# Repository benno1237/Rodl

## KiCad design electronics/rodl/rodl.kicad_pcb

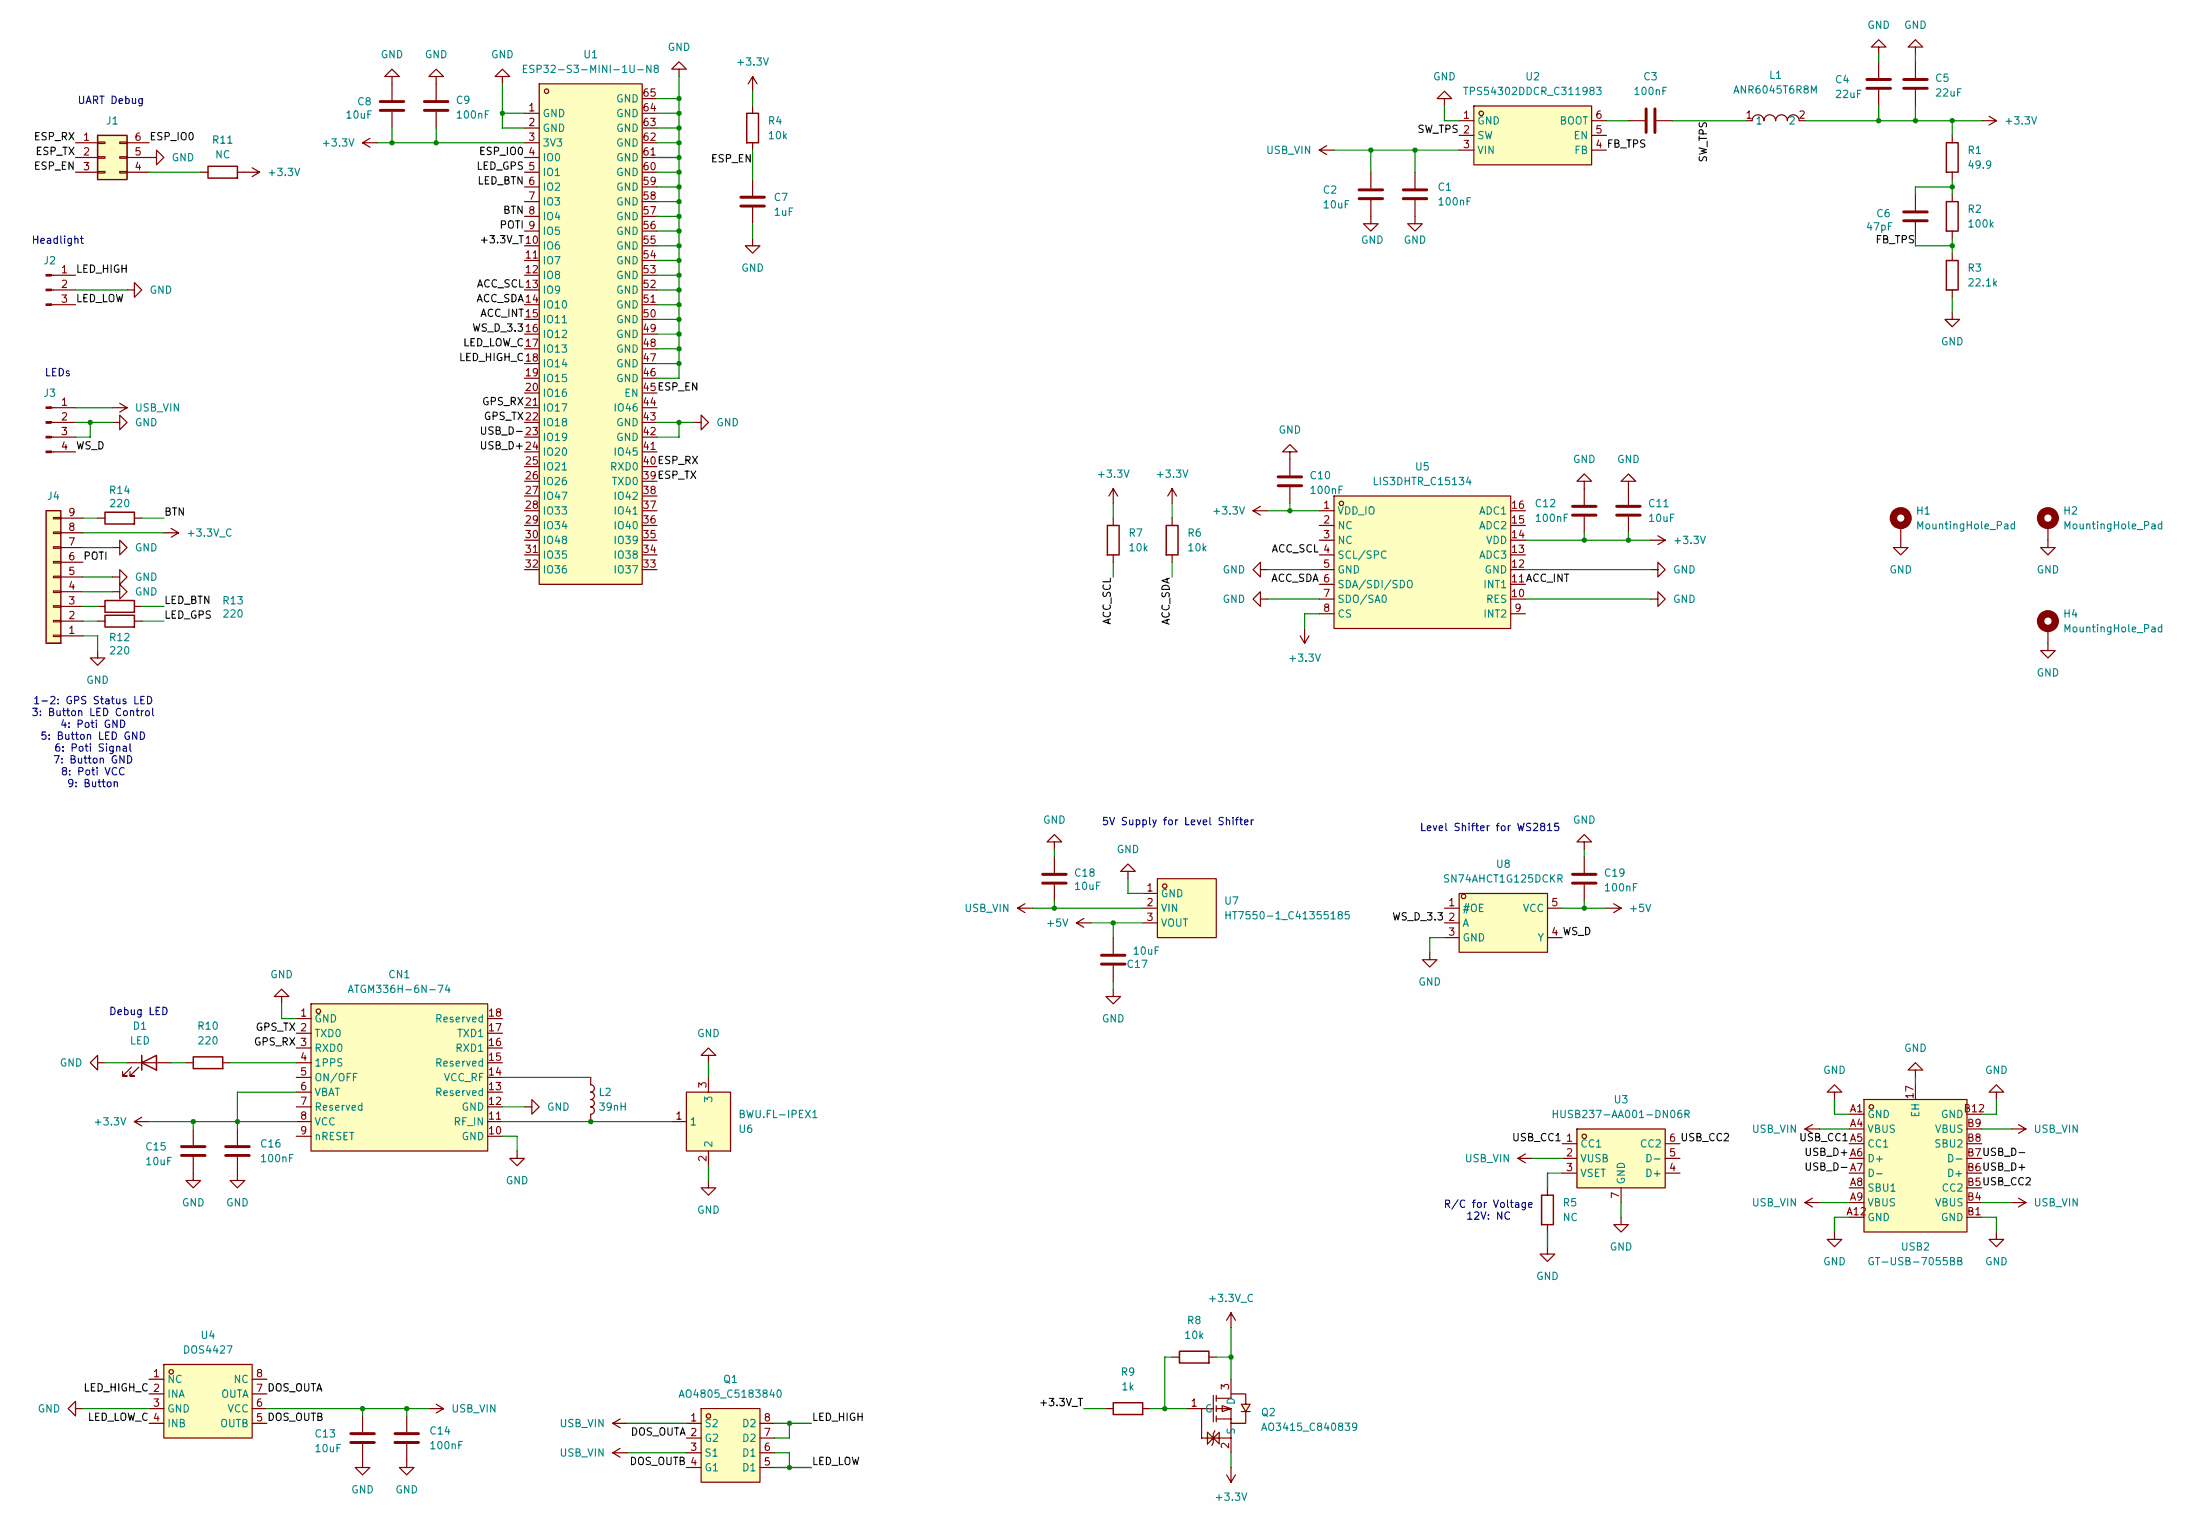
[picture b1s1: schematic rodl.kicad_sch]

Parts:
C1, C3, C9, C10, C12, C14, C16, C19: 100nF; C_0603_1608Metric
C2, C8, C11, C13, C15, C17, C18: 10uF; C_0603_1608Metric
C4, C5: 22uF; C_0805_2012Metric
C6: 47pF; C_0603_1608Metric
C7: 1uF; C_0603_1608Metric
CN1: ATGM336H-6N-74; COMM-SMD_18P-L10.1-W9.7-P1.1-TL_L76-LB; LCSC Part C5804601
D1: LED; LED_0603_1608Metric
H1, H2, H4: MountingHole_Pad; MountingHole_2.5mm_Pad_TopOnly
J1: PinSocket_2x03_P2.54mm_Vertical
J2: Conn_01x03_Pin; PinSocket_1x03_P2.00mm_Vertical
J3: Conn_01x04_Pin; PinSocket_1x04_P2.00mm_Vertical
J4: Conn_01x09; Connector_Rodl
L1: ANR6045T6R8M; IND-SMD_L6.0-W6.0_ANR6045; LCSC Part C6808110
L2: 39nH; L_0603_1608Metric
Q1: AO4805_C5183840; SOP-8_L4.9-W3.9-P1.27-LS6.0-BL; LCSC Part C5183840
Q2: AO3415_C840839; SOT-23-3_L2.9-W1.6-P1.90-LS2.8-BR; LCSC Part C840839
R1: 49.9; R_0603_1608Metric
R2: 100k; R_0603_1608Metric
R3: 22.1k; R_0603_1608Metric
R4, R6, R7, R8: 10k; R_0603_1608Metric
R5, R11: NC; R_0603_1608Metric
R9: 1k; R_0603_1608Metric
R10, R12, R13, R14: 220; R_0603_1608Metric
U1: ESP32-S3-MINI-1U-N8; BULETM-SMD_ESPRESSIF_ESP32-S3-MINI-1U-N8; LCSC Part C2980299
U2: TPS54302DDCR_C311983; SOT-23-6_L2.9-W1.6-P0.95-LS2.8-BL; LCSC Part C311983
U3: HUSB237-AA001-DN06R; TDFN-6_L2.0-W2.0-P0.65-TL-EP; LCSC Part C22373734
U4: DOS4427; SOIC-8_L5.0-W4.0-P1.27-LS6.0-BL; LCSC Part C42395831
U5: LIS3DHTR_C15134; LGA-16_L3.0-W3.0-P0.50-TL; LCSC Part C15134
U6: BWU.FL-IPEX1; IPEX-SMD_BWIPX-1-001E; LCSC Part C5137195
U7: HT7550-1_C41355185; SOT-89-3_L4.5-W2.4-P1.50-LS4.0-BR; LCSC Part C41355185
U8: SN74AHCT1G125DCKR; SC-70-5_L2.0-W1.3-P0.65-LS2.1-BL; LCSC Part C350557
USB2: GT-USB-7055BB; USB-C-TH_GT-USB-7055BB; LCSC Part C7450621

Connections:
+3.3V: C4.2, C5.2, C8.1, C9.1, C10.1, C11.1, C12.1, C15.1, C16.1, CN1.6 (VBAT), CN1.8 (VCC), L1.2, Q2.2 (S), R1.1, R4.1, R6.1, R7.1, R11.2, U1.3 (3V3), U5.1 (VDD_IO), U5.8 (CS), U5.14 (VDD)
+3.3V_C: J4.8, Q2.3 (D), R8.2
+5V: C17.1, C19.1, U7.3 (VOUT), U8.5 (VCC)
/+3.3V_T: R9.1, U1.10 (IO6)
/ACC_INT: U1.15 (IO11), U5.11 (INT1)
/ACC_SCL: R7.2, U1.13 (IO9), U5.4 (SCL/SPC)
/ACC_SDA: R6.2, U1.14 (IO10), U5.6 (SDA/SDI/SDO)
/BTN: R14.2, U1.8 (IO4)
/DOS_OUTA: Q1.2 (G2), U4.7 (OUTA)
/DOS_OUTB: Q1.4 (G1), U4.5 (OUTB)
/ESP_EN: C7.1, J1.3, R4.2, U1.45 (EN)
/ESP_IO0: J1.6, U1.4 (IO0)
/ESP_RX: J1.1, U1.40 (RXD0)
/ESP_TX: J1.2, U1.39 (TXD0)
/FB_TPS: C6.2, R2.2, R3.1, U2.4 (FB)
/GPS_RX: CN1.3 (RXD0), U1.21 (IO17)
/GPS_TX: CN1.2 (TXD0), U1.22 (IO18)
/LED_BTN: R13.2, U1.6 (IO2)
/LED_GPS: R12.2, U1.5 (IO1)
/LED_HIGH: J2.1, Q1.7 (D2), Q1.8 (D2)
/LED_HIGH_C: U1.18 (IO14), U4.2 (INA)
/LED_LOW: J2.3, Q1.5 (D1), Q1.6 (D1)
/LED_LOW_C: U1.17 (IO13), U4.4 (INB)
/POTI: J4.6, U1.9 (IO5)
/SW_TPS: C3.2, L1.1, U2.2 (SW)
/USB_CC1: U3.1 (CC1), USB2.A5 (CC1)
/USB_CC2: U3.6 (CC2), USB2.B5 (CC2)
/USB_D+: U1.24 (IO20), USB2.A6 (D+), USB2.B6 (D+)
/USB_D-: U1.23 (IO19), USB2.A7 (D-), USB2.B7 (D-)
/WS_D: J3.4, U8.4 (Y)
/WS_D_3.3: U1.16 (IO12), U8.2 (A)
GND: C1.2, C2.2, C4.1, C5.1, C7.2, C8.2, C9.2, C10.2, C11.2, C12.2, C13.2, C14.2, C15.2, C16.2, C17.2, C18.1, C19.2, CN1.1 (GND), CN1.10 (GND), CN1.12 (GND), D1.1 (K), H1.1, H2.1, H4.1, J1.5, J2.2, J3.2, J3.3, J4.1, J4.4, J4.5, J4.7, R3.2, R5.2, U1.1 (GND), U1.2 (GND), U1.42 (GND), U1.43 (GND), U1.46 (GND), U1.47 (GND), U1.48 (GND), U1.49 (GND), U1.50 (GND), U1.51 (GND), U1.52 (GND), U1.53 (GND), U1.54 (GND), U1.55 (GND), U1.56 (GND), U1.57 (GND), U1.58 (GND), U1.59 (GND), U1.60 (GND), U1.61 (GND), U1.62 (GND), U1.63 (GND), U1.64 (GND), U1.65 (GND), U2.1 (GND), U3.7 (GND), U4.3 (GND), U5.5 (GND), U5.7 (SDO/SA0), U5.10 (RES), U5.12 (GND), U6.2, U6.3, U7.1 (GND), U8.3 (GND), USB2.17 (EH), USB2.A1 (GND), USB2.A12 (GND), USB2.B1 (GND), USB2.B12 (GND)
unnamed: C6.1, R1.2, R2.1
unnamed: CN1.4 (1PPS), R10.2
unnamed: CN1.11 (RF_IN), L2.2, U6.1
unnamed: CN1.14 (VCC_RF), L2.1
unnamed: D1.2 (A), R10.1
unnamed: J1.4, R11.1
unnamed: J4.2, R12.1
unnamed: J4.3, R13.1
unnamed: J4.9, R14.1
unnamed: Q2.1 (G), R8.1, R9.2
unnamed: C3.1, U2.6 (BOOT)
unnamed: R5.1, U3.3 (VSET)
USB_VIN: C1.1, C2.1, C13.1, C14.1, C18.2, J3.1, Q1.1 (S2), Q1.3 (S1), U2.3 (VIN), U3.2 (VUSB), U4.6 (VCC), U7.2 (VIN), USB2.A4 (VBUS), USB2.A9 (VBUS), USB2.B4 (VBUS), USB2.B9 (VBUS)

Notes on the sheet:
LEDs
R/C for Voltage 12V: NC
Headlight
1-2: GPS Status LED 3: Button LED Control 4: Poti GND 5: Button LED GND 6: Poti Signal 7: Button GND 8: Poti VCC 9: Button
Level Shifter for WS2815
Debug LED
UART Debug
5V Supply for Level Shifter

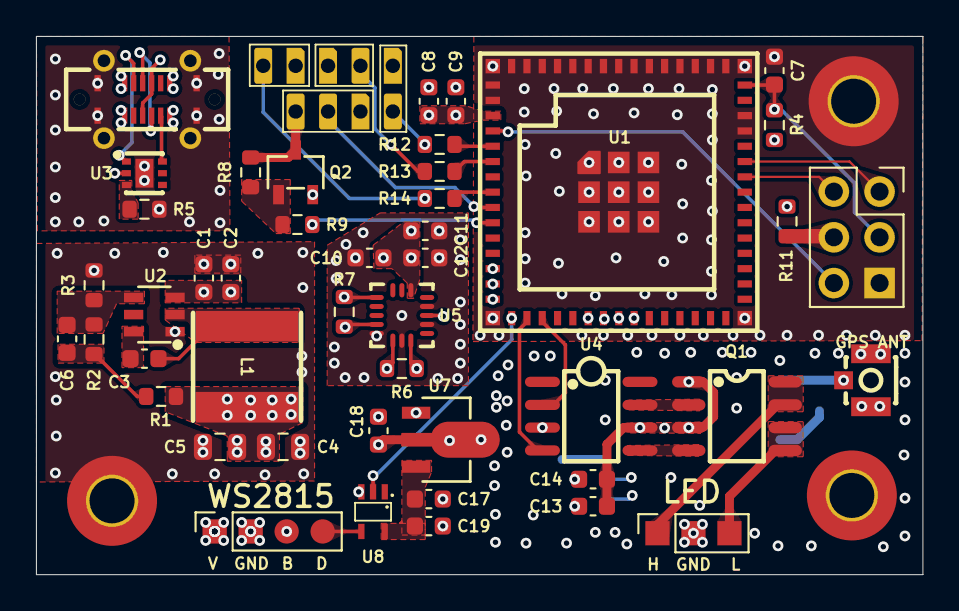
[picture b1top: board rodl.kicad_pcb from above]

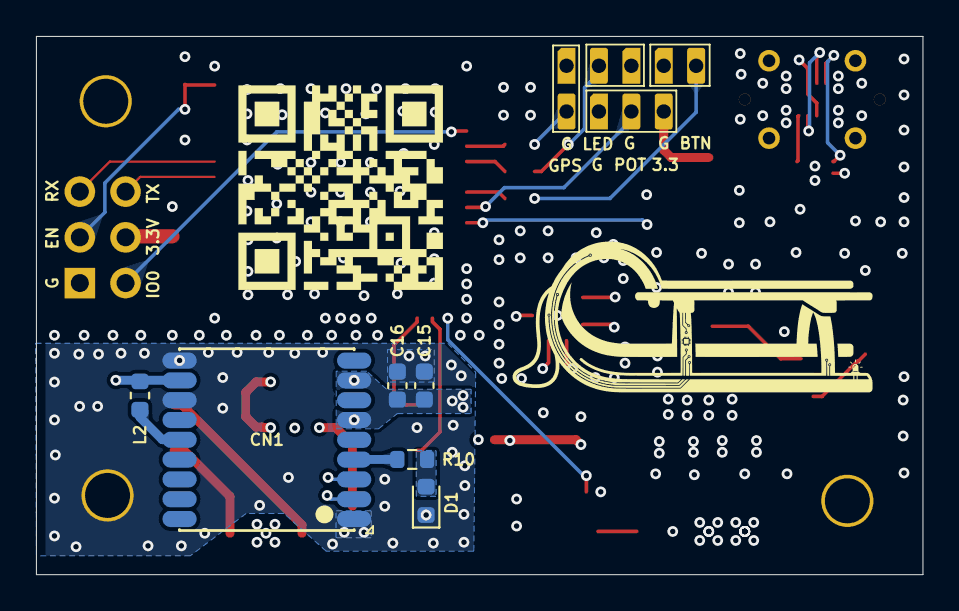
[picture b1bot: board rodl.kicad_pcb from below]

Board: 6 copper layers, 49.2 x 29.9 mm, 55 parts (6 on the bottom side), 45 nets.

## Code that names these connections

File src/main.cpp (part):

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// Pin Definitions
constexpr uint8_t BUTTON_PIN = 4;        // Main control button
constexpr uint8_t LED_BUTTON_PIN = 2;       // Potentiometer enable pin
constexpr uint8_t LED_LOW_PIN = 13;      // Low beam LED driver
constexpr uint8_t LED_HIGH_PIN = 14;     // High beam LED driver
constexpr uint8_t POT_PIN = 5;           // Potentiometer pin
constexpr uint8_t POT_ENABLE = 6;       // Pot enable pin
constexpr uint8_t ACC_SCL_PIN = 9;      // Accelerometer clock pin
constexpr uint8_t ACC_SDA_PIN = 10;      // Accelerometer data pin
constexpr uint8_t ACC_INT_PIN = 11;      // Accelerometer interrupt pin

// GPS Pin Definitions
constexpr uint8_t GPS_RX_PIN = 17;       // GPS RX (ESP32 TX)
constexpr uint8_t GPS_TX_PIN = 18;       // GPS TX (ESP32 RX)

// LED Strip Settings
constexpr uint8_t LED_PIN = 12;          // WS2815 LED control pin
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
  // Set up PWM for MOSFET drivers
  ledcSetup(PWM_CHANNEL_LOW, PWM_FREQ, PWM_RESOLUTION);
  ledcAttachPin(LED_LOW_PIN, PWM_CHANNEL_LOW);
  // ledcAttachChannel(LED_LOW_PIN, PWM_FREQ, PWM_RESOLUTION, PWM_CHANNEL_LOW);

  ledcSetup(PWM_CHANNEL_HIGH, PWM_FREQ, PWM_RESOLUTION);
  ledcAttachPin(LED_HIGH_PIN, PWM_CHANNEL_HIGH);
  // ledcAttachChannel(LED_HIGH_PIN, PWM_FREQ, PWM_RESOLUTION, PWM_CHANNEL_HIGH);

  pinMode(POT_PIN, INPUT);
  pinMode(POT_ENABLE, OUTPUT);
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
  // Initialize accelerometer
#ifdef ACC
  Wire.setPins(ACC_SDA_PIN, ACC_SCL_PIN);
  lis.begin(Wire, 0x18); // Initialize the LIS3DHTR sensor
  if (!lis.isConnection())
  { // 0x18 is the default I2C address
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  }

  // Initialize GPS serial
  gpsSerial.begin(GPS_BAUDRATE, SERIAL_8N1, GPS_RX_PIN, GPS_TX_PIN);

  // Configure GPS for 10Hz update rate
  // ATGM336H-6N-6N configuration commands via UBX protocol
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
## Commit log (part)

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2022-02-28 init
2022-03-24 WS2812FX support
2022-03-24 Color conversion for ws2812 leds
2022-03-24 Finalized led support, fixed hsv to rgb
2022-03-29 Added electronics files
2022-03-29 implementing color control
2023-01-05 Fixed color control
2023-01-07 Rewrite christmas holidays
2023-01-10 implemented color rollover
2023-02-11 added optional temp readings
2023-02-11 voltage divider setup
2024-10-11 adapt to custom pcb
2024-10-13 cleanup
2024-10-13 add accelerometer (lis3dhtr)
2024-10-13 added bluetooth and a few bluetooth configuration commands
2024-10-13 individual get commands for each config parameter
2024-10-13 added parameters to toggle auto shutdown/start on accel change
2024-10-16 made logging optional
2024-10-16 added ble functions (incomplete)
2025-01-25 fixed accelerometer
2025-02-04 auto shutdown/startup changes
2025-12-10 add electronics to git repo
2025-12-10 add gitignore for kicad
2025-12-10 Revert "add electronics to git repo"
    This reverts commit 0c6e46c7c86016e74241b5d5c0aefd849a76f06a.
2025-12-10 Reapply "add electronics to git repo"
    This reverts commit d3dfa0931eba71c41fedfbb0a7556fad42c364d6.
2025-12-10 fix gitignore
2025-12-10 readd 3d shapes
2025-12-10 remove .vscode
2025-12-20 new electronic version
2026-01-16 finish pcb
2026-01-18 update for new board
2026-01-18 update flash to 8MB
2026-02-10 add gps code
2026-02-20 improve gps logging
2026-02-20 change structure
2026-02-20 gitignre
2026-02-20 even more gitignore
2026-02-20 create app
2026-02-20 rename app
2026-02-20 fluter deps
2026-02-20 add ble functions
2026-02-26 fix gps pins
2026-02-26 gps debug code
2026-02-26 add app code
2026-02-27 async csv parsing
2026-02-27 styling improvements
2026-03-01 work on slider styling
2026-03-01 new colorpicker panel
2026-03-01 fancy effect selection widget
2026-03-01 deprecation warnings
2026-03-01 add favourite sled star
2026-03-01 init GPS
2026-03-01 GPS start/stop + ride integration
2026-03-02 GPS background worker
2026-03-02 untested iOS GPS background runner
2026-03-02 fix deprecation warnings
2026-03-03 implement GPS tile caching and tile bundling
2026-03-03 remove .xml from gitignore
2026-03-03 implement .gpx reference tracks, cache management, remove bundled maps
2026-03-03 create sled - ride mapping + sled settings file
2026-03-04 implement username
2026-03-04 Load sleds from json
2026-03-04 init tracks section
2026-03-04 work on track segments + implement leaderboard
2026-03-05 send gps/accel via bluetooth
2026-03-05 receive gps/accel from bluetooth
2026-03-06 implement gpx export
2026-03-06 increase gps accuracy
2026-03-06 add speed profile
2026-03-06 tweak plot spacings. broke ytick label alignment
2026-03-08 init track matching + cleanup
2026-03-13 init CAD models
2026-03-21 include additional data in gpx export/import
